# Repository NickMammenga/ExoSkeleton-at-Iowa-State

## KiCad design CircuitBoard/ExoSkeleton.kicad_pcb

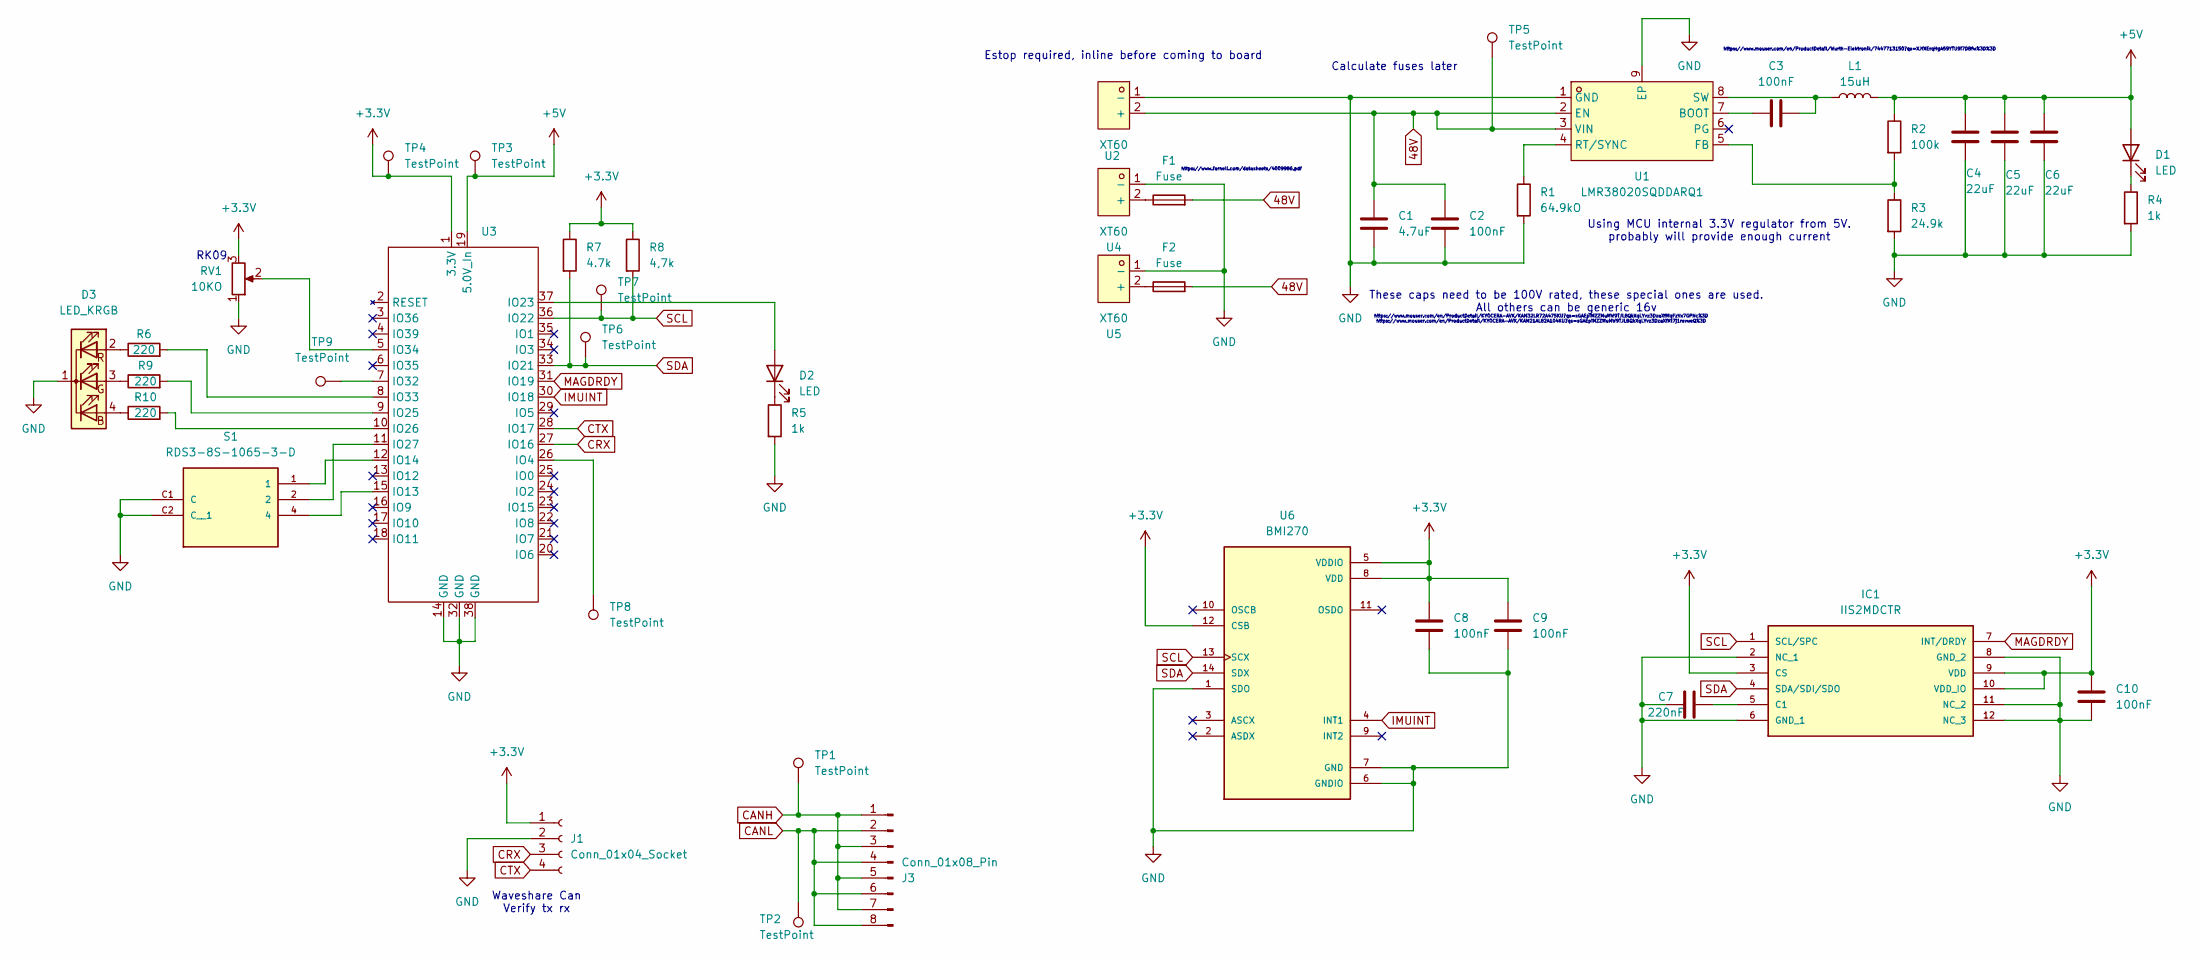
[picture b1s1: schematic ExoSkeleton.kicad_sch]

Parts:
C1: 4.7uF; C_1210_3225Metric
C2: 100nF; C_0805_2012Metric
C3, C8, C9, C10: 100nF; C_0603_1608Metric
C4, C5, C6: 22uF; C_0603_1608Metric
C7: 220nF; C_0603_1608Metric
D1, D2: LED; LED_0603_1608Metric
D3: LED_KRGB; LED_D5.0mm-4_RGB
F1, F2: Fuse; SMDFuse MP012924
IC1: IIS2MDCTR; MOUSER_PART_NUMBER 511-IIS2MDCTR
J1: Conn_01x04_Socket; PinSocket_1x04_P2.54mm_Horizontal
J3: Conn_01x08_Pin; PinSocket_1x08_P2.54mm_Vertical
L1: 15uH; L_Wuerth_HCI-1030
R1: 64.9kO; R_0603_1608Metric
R2: 100k; R_0603_1608Metric
R3: 24.9k; R_0603_1608Metric
R4, R5: 1k; R_0603_1608Metric
R6, R9, R10: 220; R_0603_1608Metric
R7: 4.7k; R_0603_1608Metric
R8: 4,7k; R_0603_1608Metric
RV1: 10KO; Potentiometer_Alps_RK09K_Single_Vertical
S1: RDS3-8S-1065-3-D; SW_RDS3-8S-1065-3-D; MPN RDS3-8S-1065-3-D
TP1, TP2, TP3, TP4, TP5, TP6, TP7, TP8, TP9: TestPoint; TestPoint_Pad_D2.0mm
U1: LMR38020SQDDARQ1; SOIC-8_L4.9-W3.9-P1.27-LS6.0-BL-EP3.4; MPN LMR38020SQDDARQ1; LCSC Part C18212861
U2, U4, U5: XT60; AMASS_XT60PW-M_1x02_P7.20mm_Horizontal; MPN XT60-M.; LCSC Part C98733
U3: ESP32 38Pin Slim
U6: BMI270; XDCR_BMI270

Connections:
48V: C1.1, C2.1, F1.2, F2.2, TP5.1 (1_1), U1.2 (EN), U1.3 (VIN), U2.2 (+)
+3.3V: C8.1, C9.1, C10.1, IC1.3 (CS), IC1.9 (VDD), IC1.10 (VDD_IO), J1.1, R7.1, R8.1, RV1.3, TP4.1 (1_1), U3.1 (3.3V), U6.5 (VDDIO), U6.8 (VDD), U6.12 (CSB)
+5V: C4.1, C5.1, C6.1, D1.2 (A), L1.2, R2.1, TP3.1 (1_1), U3.19 (5.0V_In)
CANH: J3.1, J3.3, J3.5, J3.7, TP1.1 (1_1)
CANL: J3.2, J3.4, J3.6, J3.8, TP2.1 (1_1)
CRX: J1.3, U3.27 (IO16)
CTX: J1.4, U3.28 (IO17)
GND: C1.2, C2.2, C4.2, C5.2, C6.2, C7.1, C8.2, C9.2, C10.2, D3.1 (K), IC1.2 (NC_1), IC1.6 (GND_1), IC1.8 (GND_2), IC1.11 (NC_2), IC1.12 (NC_3), J1.2, R1.2, R3.2, R4.2, R5.2, RV1.1, S1.C1 (C), S1.C2 (C__1), U1.1 (GND), U1.9 (EP), U2.1 (-), U3.14 (GND), U3.32 (GND), U3.38 (GND), U4.1 (-), U5.1 (-), U6.1 (SDO), U6.6 (GNDIO), U6.7 (GND)
IMUINT: U3.30 (IO18), U6.4 (INT1)
MAGDRDY: IC1.7 (INT/DRDY), U3.31 (IO19)
unnamed: D1.1 (K), R4.1
unnamed: D2.2 (A), U3.37 (IO23)
unnamed: D2.1 (K), R5.1
unnamed: D3.4 (BA), R10.1
unnamed: D3.3 (GA), R9.1
unnamed: D3.2 (RA), R6.1
unnamed: C7.2, IC1.5 (C1)
unnamed: C3.1, U1.7 (BOOT)
unnamed: R2.2, R3.1, U1.5 (FB)
unnamed: R1.1, U1.4 (RT/SYNC)
unnamed: C3.2, L1.1, U1.8 (SW)
unnamed: TP8.1 (1_1), U3.26 (IO4)
unnamed: S1.4, U3.15 (IO13)
unnamed: S1.1, U3.12 (IO14)
unnamed: R9.2, U3.9 (IO25)
unnamed: R10.2, U3.10 (IO26)
unnamed: S1.2, U3.11 (IO27)
unnamed: TP9.1 (1_1), U3.7 (IO32)
unnamed: R6.2, U3.8 (IO33)
unnamed: RV1.2, U3.5 (IO34)
unnamed: F1.1, U4.2 (+)
unnamed: F2.1, U5.2 (+)
SCL: IC1.1 (SCL/SPC), R8.2, TP7.1 (1_1), U3.36 (IO22), U6.13 (SCX)
SDA: IC1.4 (SDA/SDI/SDO), R7.2, TP6.1 (1_1), U3.33 (IO21), U6.14 (SDX)

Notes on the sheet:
Calculate fuses later
These caps need to be 100V rated, these special ones are used. All others can be generic 16v
https://www.mouser.com/en/ProductDetail/Wurth-Elektronik/7447713150?qs=XJfXErqHgA59YTU9i7DBfw%3D%3D
https://www.mouser.com/en/ProductDetail/KYOCERA-AVX/KAM32LR72A475KU?qs=sGAEpiMZZMuMW9TJLBQkXqLYvz3DzaXfMqFzVx7GPNc%3D https://www.mouser.com/en/ProductDetail/KYOCERA-AVX/KAM21AL82A104KU?qs=sGAEpiMZZMuMW9TJLBQkXqLYvz3DzaXfXt7j1rsvweQ%3D
Using MCU internal 3.3V regulator from 5V. probably will provide enough current
Waveshare Can Verify tx rx
https://www.farnell.com/datasheets/4009986.pdf
RK09
Estop required, inline before coming to board

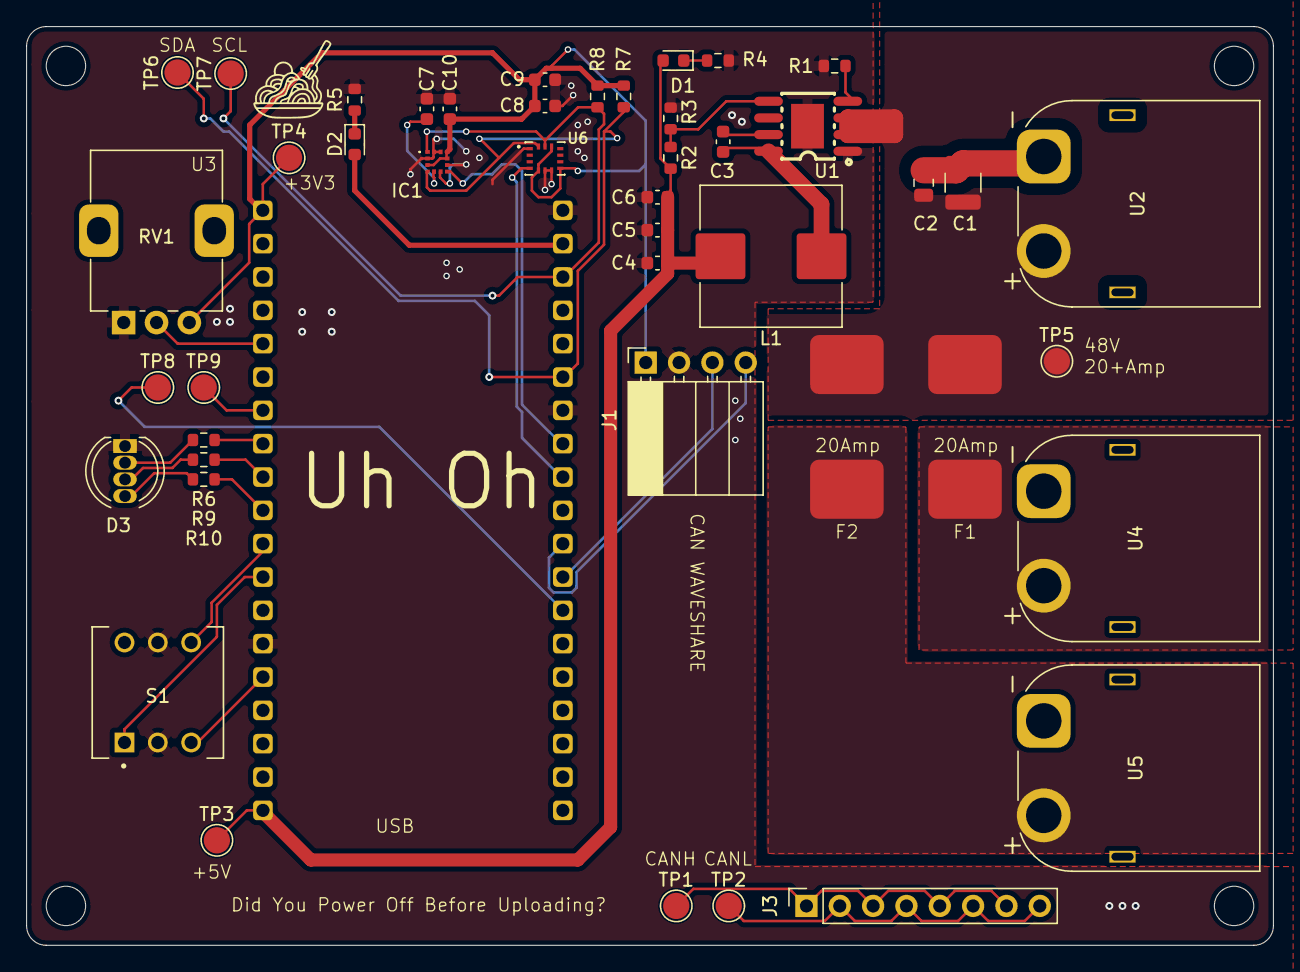
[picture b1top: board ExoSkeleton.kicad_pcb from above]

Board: 2 copper layers, 95.0 x 70.0 mm, 46 parts (0 on the bottom side), 34 nets.
